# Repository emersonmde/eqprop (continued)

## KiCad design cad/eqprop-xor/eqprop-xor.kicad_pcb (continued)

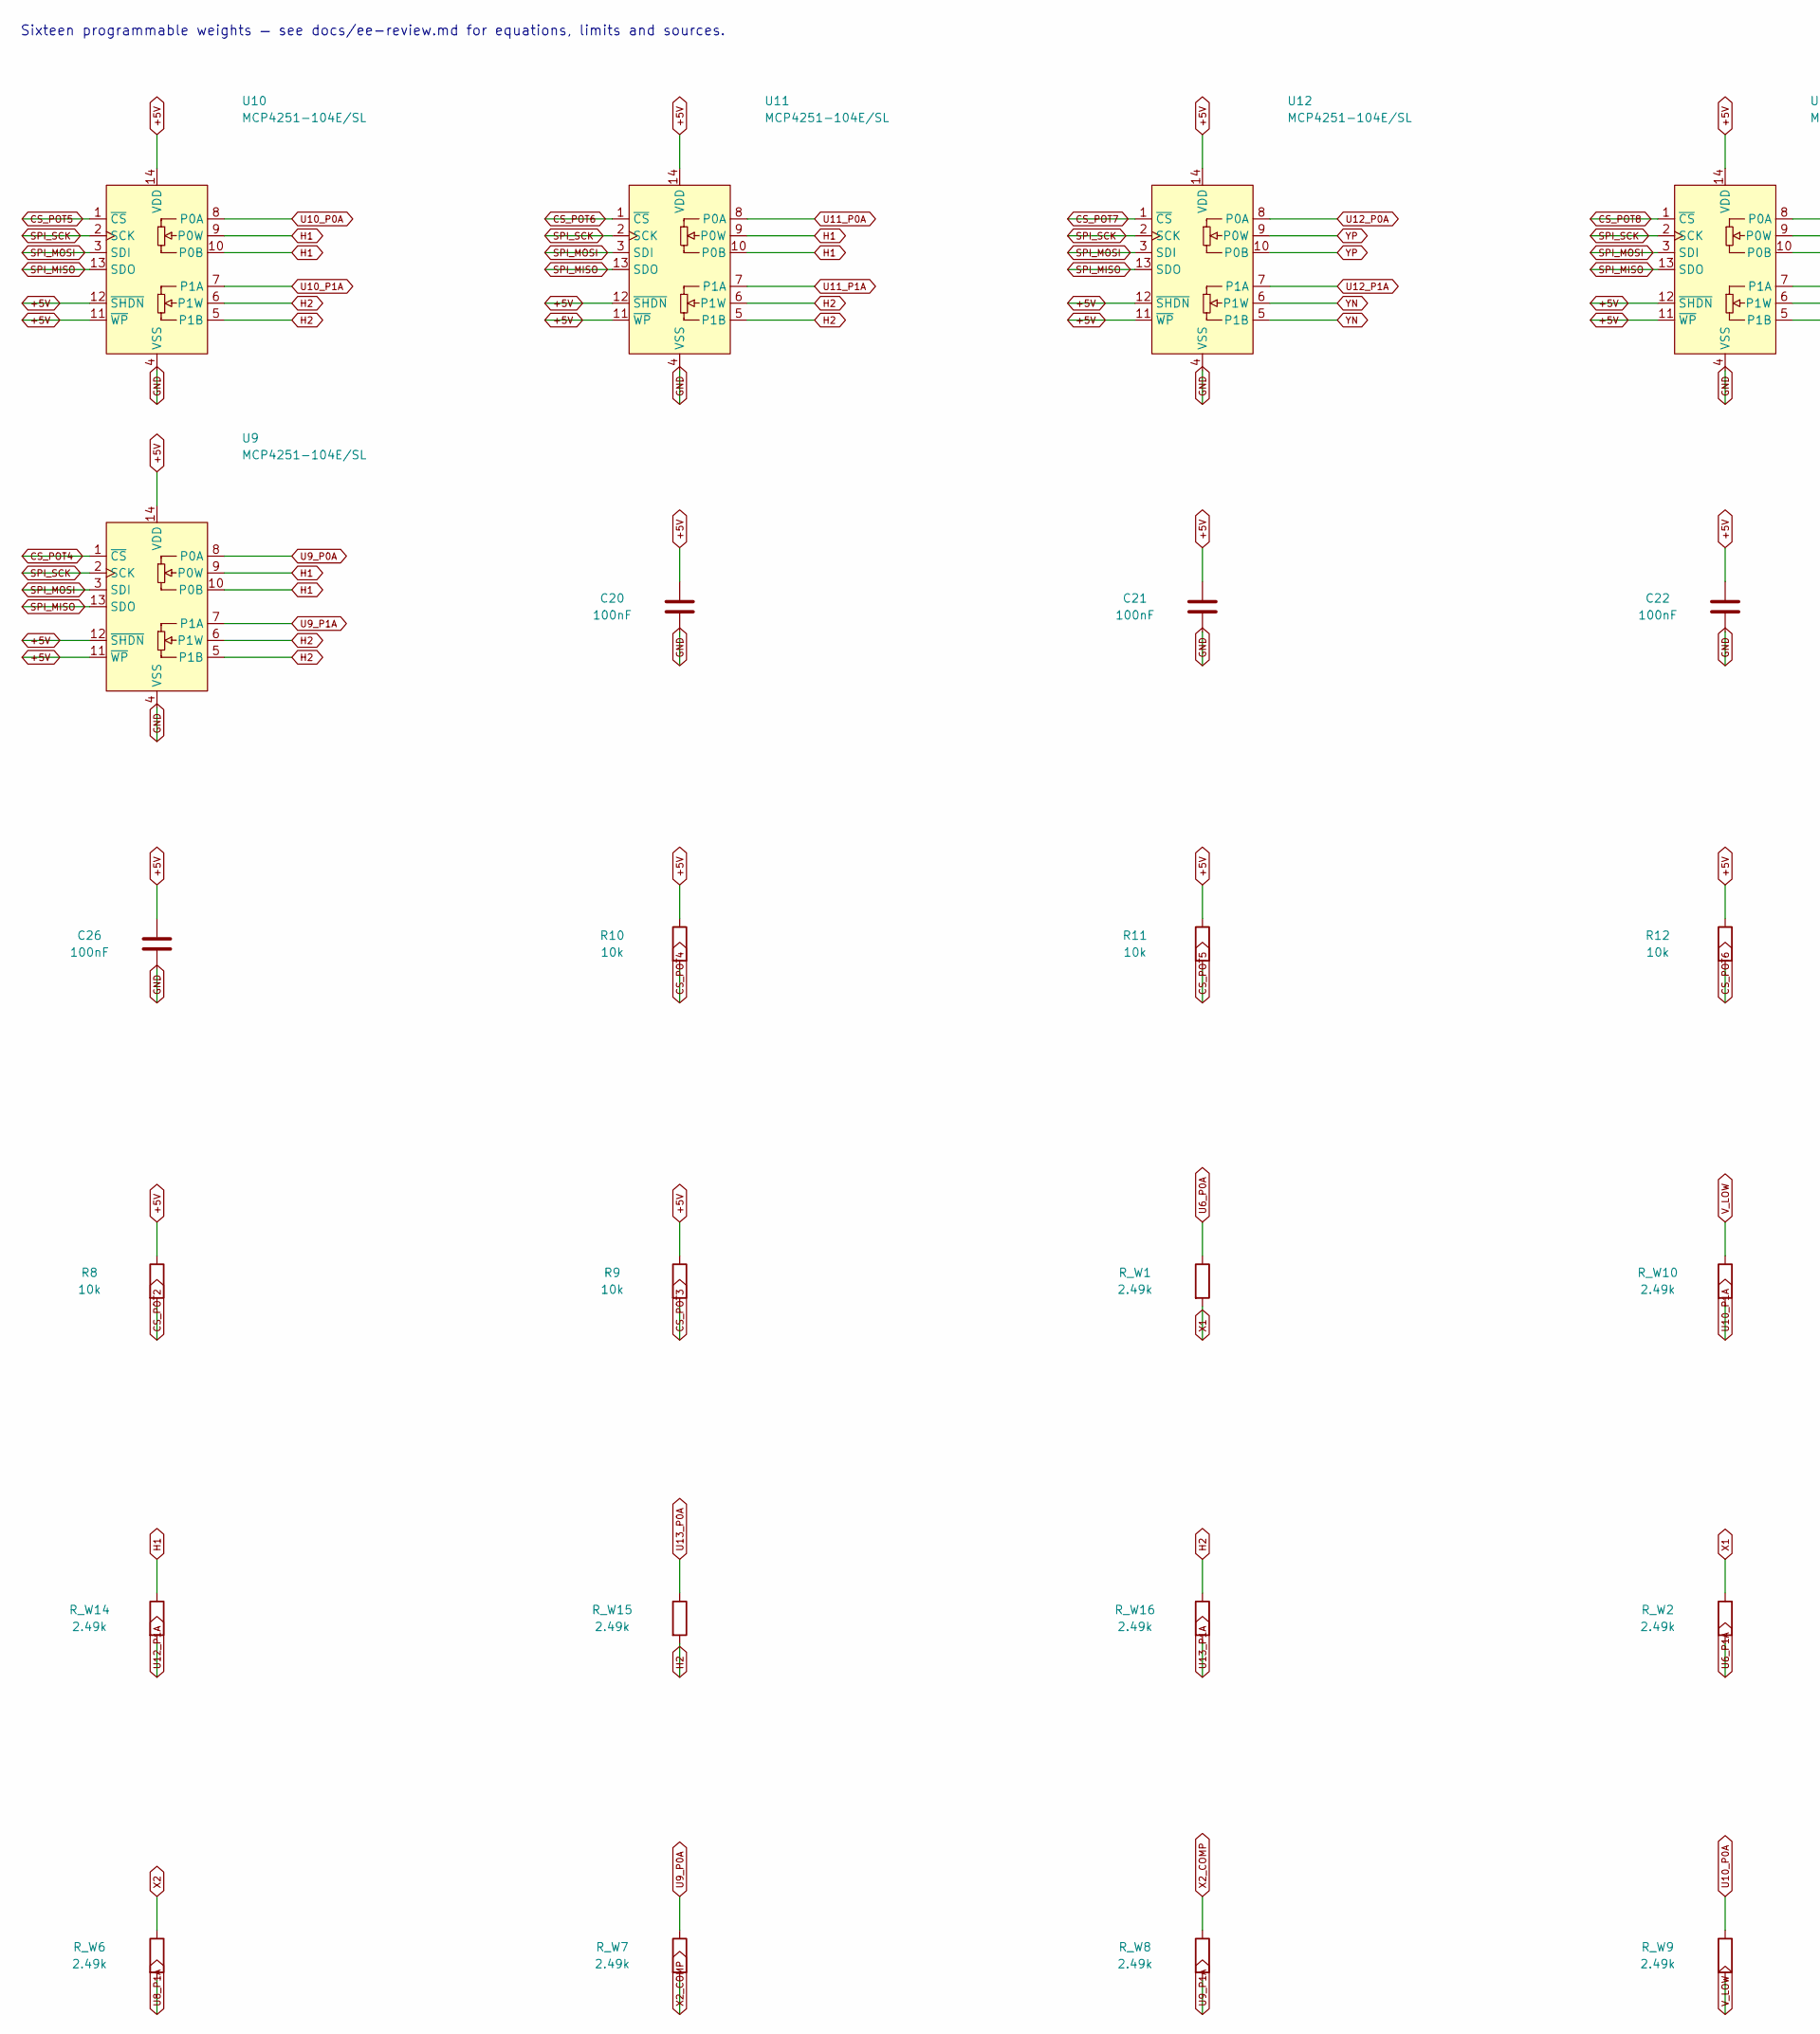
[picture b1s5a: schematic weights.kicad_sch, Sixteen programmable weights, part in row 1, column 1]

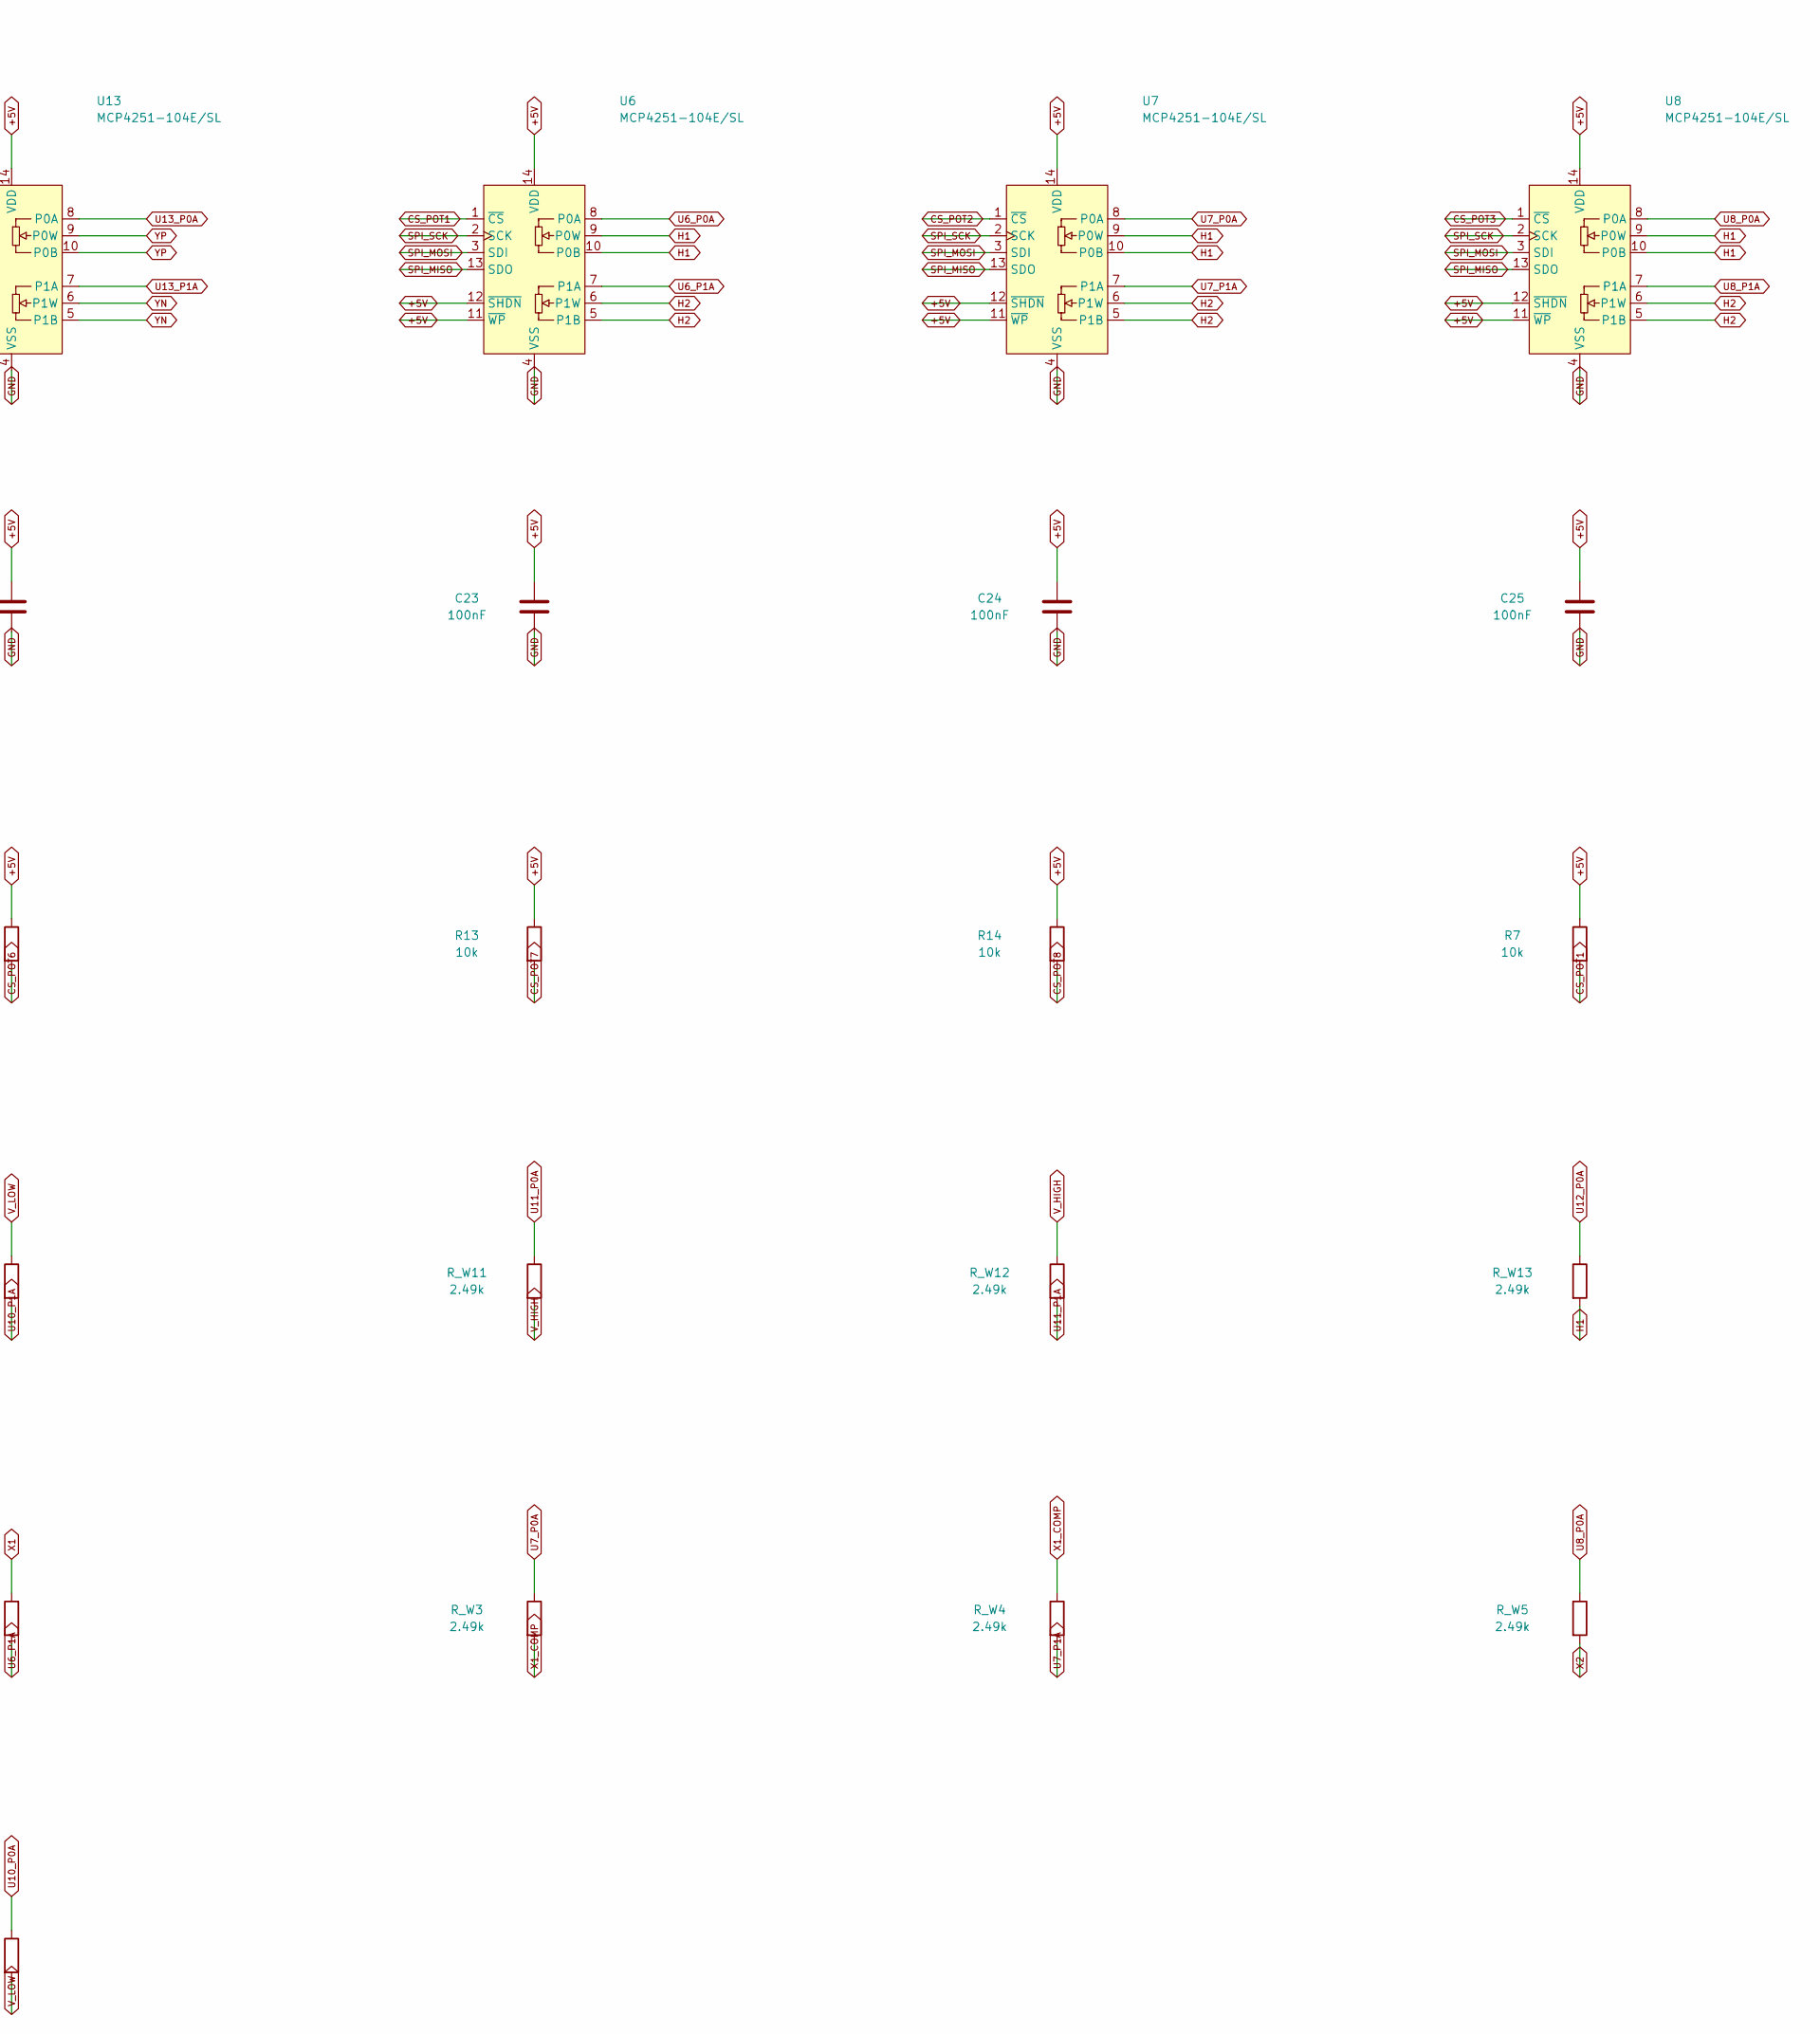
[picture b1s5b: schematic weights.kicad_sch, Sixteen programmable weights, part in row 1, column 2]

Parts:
C20, C21, C22, C23, C24, C25, C26: 100nF; C_0805_2012Metric; MPN C0805C104K5RACTU
R7, R8, R9, R10, R11, R12, R13, R14: 10k; R_0805_2012Metric; Tolerance 1%; MPN CRCW080510K0FKEA
R_W1, R_W2, R_W3, R_W4, R_W5, R_W6, R_W7, R_W8, R_W9, R_W10, R_W11, R_W12, R_W13, R_W14, R_W15, R_W16: 2.49k; R_0805_2012Metric; Tolerance 1%; MPN CRCW08052K49FKEA
U6, U7, U8, U9, U10, U11, U12, U13: MCP4251-104E/SL; SOIC-14_3.9x8.7mm_P1.27mm; MPN MCP4251-104E/SL

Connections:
+5V: C20.1, C21.1, C22.1, C23.1, C24.1, C25.1, C26.1, R7.1, R8.1, R9.1, R10.1, R11.1, R12.1, R13.1, R14.1, U6.11 (~WP), U6.12 (~SHDN), U6.14 (VDD), U7.11 (~WP), U7.12 (~SHDN), U7.14 (VDD), U8.11 (~WP), U8.12 (~SHDN), U8.14 (VDD), U9.11 (~WP), U9.12 (~SHDN), U9.14 (VDD), U10.11 (~WP), U10.12 (~SHDN), U10.14 (VDD), U11.11 (~WP), U11.12 (~SHDN), U11.14 (VDD), U12.11 (~WP), U12.12 (~SHDN), U12.14 (VDD), U13.11 (~WP), U13.12 (~SHDN), U13.14 (VDD); also elsewhere on the board
CS_POT1: R7.2, U6.1 (~CS); also elsewhere on the board
CS_POT2: R8.2, U7.1 (~CS); also elsewhere on the board
CS_POT3: R9.2, U8.1 (~CS); also elsewhere on the board
CS_POT4: R10.2, U9.1 (~CS); also elsewhere on the board
CS_POT5: R11.2, U10.1 (~CS); also elsewhere on the board
CS_POT6: R12.2, U11.1 (~CS); also elsewhere on the board
CS_POT7: R13.2, U12.1 (~CS); also elsewhere on the board
CS_POT8: R14.2, U13.1 (~CS); also elsewhere on the board
GND: C20.2, C21.2, C22.2, C23.2, C24.2, C25.2, C26.2, U6.4 (VSS), U7.4 (VSS), U8.4 (VSS), U9.4 (VSS), U10.4 (VSS), U11.4 (VSS), U12.4 (VSS), U13.4 (VSS); also elsewhere on the board
H1: R_W13.2, R_W14.1, U6.9 (P0W), U6.10 (P0B), U7.9 (P0W), U7.10 (P0B), U8.9 (P0W), U8.10 (P0B), U9.9 (P0W), U9.10 (P0B), U10.9 (P0W), U10.10 (P0B), U11.9 (P0W), U11.10 (P0B); also elsewhere on the board
H2: R_W15.2, R_W16.1, U6.5 (P1B), U6.6 (P1W), U7.5 (P1B), U7.6 (P1W), U8.5 (P1B), U8.6 (P1W), U9.5 (P1B), U9.6 (P1W), U10.5 (P1B), U10.6 (P1W), U11.5 (P1B), U11.6 (P1W); also elsewhere on the board
SPI_MISO: U6.13 (SDO), U7.13 (SDO), U8.13 (SDO), U9.13 (SDO), U10.13 (SDO), U11.13 (SDO), U12.13 (SDO), U13.13 (SDO); also elsewhere on the board
SPI_MOSI: U6.3 (SDI), U7.3 (SDI), U8.3 (SDI), U9.3 (SDI), U10.3 (SDI), U11.3 (SDI), U12.3 (SDI), U13.3 (SDI); also elsewhere on the board
SPI_SCK: U6.2 (SCK), U7.2 (SCK), U8.2 (SCK), U9.2 (SCK), U10.2 (SCK), U11.2 (SCK), U12.2 (SCK), U13.2 (SCK); also elsewhere on the board
U6_P0A: R_W1.1, U6.8 (P0A)
U6_P1A: R_W2.2, U6.7 (P1A)
U7_P0A: R_W3.1, U7.8 (P0A)
U7_P1A: R_W4.2, U7.7 (P1A)
U8_P0A: R_W5.1, U8.8 (P0A)
U8_P1A: R_W6.2, U8.7 (P1A)
U9_P0A: R_W7.1, U9.8 (P0A)
U9_P1A: R_W8.2, U9.7 (P1A)
U10_P0A: R_W9.1, U10.8 (P0A)
U10_P1A: R_W10.2, U10.7 (P1A)
U11_P0A: R_W11.1, U11.8 (P0A)
U11_P1A: R_W12.2, U11.7 (P1A)
U12_P0A: R_W13.1, U12.8 (P0A)
U12_P1A: R_W14.2, U12.7 (P1A)
U13_P0A: R_W15.1, U13.8 (P0A)
U13_P1A: R_W16.2, U13.7 (P1A)
V_HIGH: R_W11.2, R_W12.1; also elsewhere on the board
V_LOW: R_W9.2, R_W10.1; also elsewhere on the board
X1: R_W1.2, R_W2.1; also elsewhere on the board
X1_COMP: R_W3.2, R_W4.1; also elsewhere on the board
X2: R_W5.2, R_W6.1; also elsewhere on the board
X2_COMP: R_W7.2, R_W8.1; also elsewhere on the board
YN: U12.5 (P1B), U12.6 (P1W), U13.5 (P1B), U13.6 (P1W); also elsewhere on the board
YP: U12.9 (P0W), U12.10 (P0B), U13.9 (P0W), U13.10 (P0B); also elsewhere on the board

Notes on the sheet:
Sixteen programmable weights — see docs/ee-review.md for equations, limits and sources.

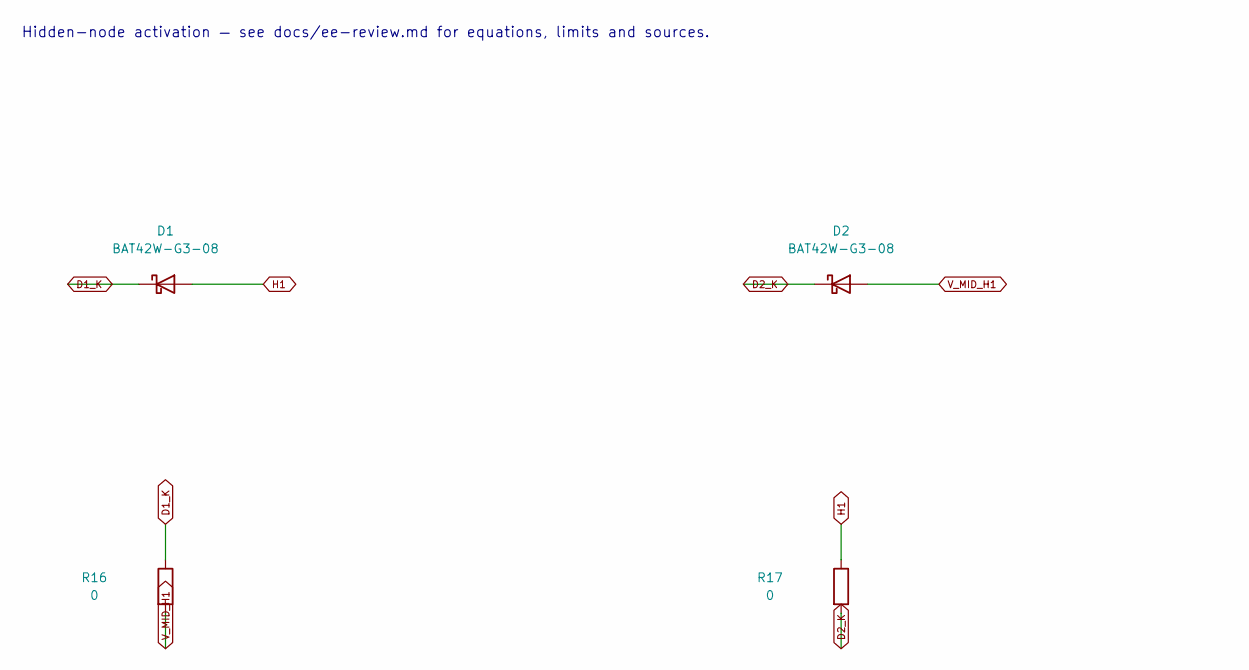
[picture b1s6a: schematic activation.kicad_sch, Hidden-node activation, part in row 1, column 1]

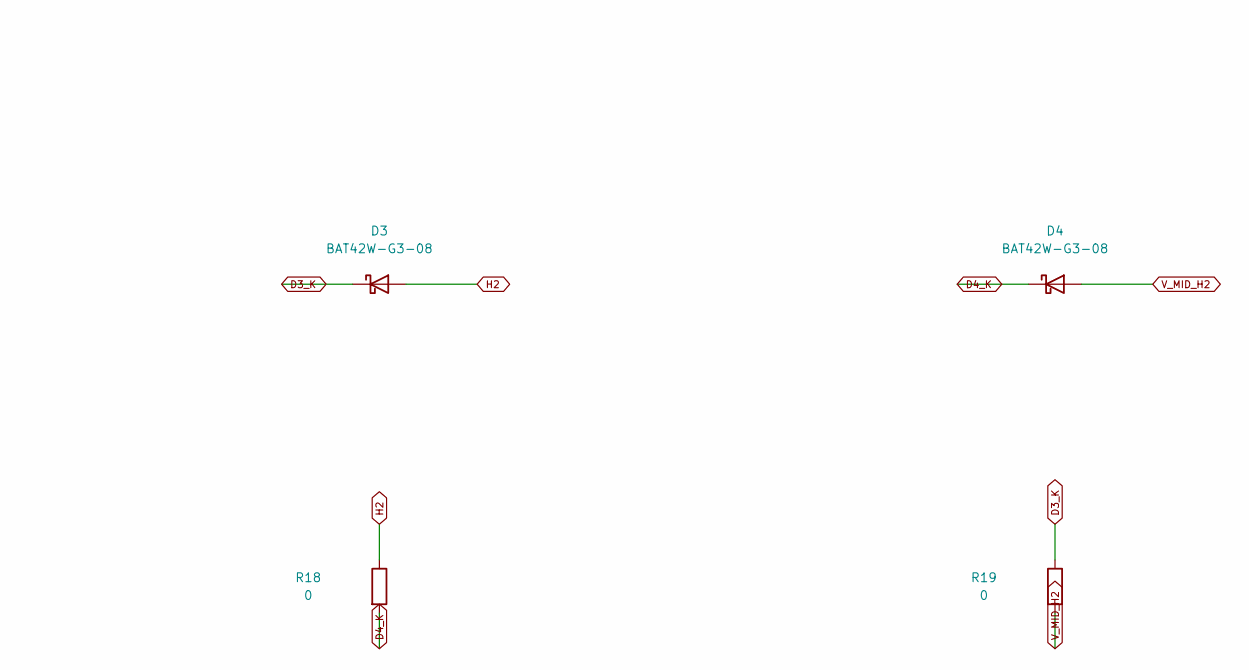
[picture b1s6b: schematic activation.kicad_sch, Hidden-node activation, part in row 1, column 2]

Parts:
D1, D2, D3, D4: BAT42W-G3-08; D_SOD-123; MPN BAT42W-G3-08
R16, R17, R18, R19: 0; R_0805_2012Metric; Tolerance Jumper; MPN CRCW08050000Z0EA

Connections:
D1_K: D1.1 (K), R16.1
D2_K: D2.1 (K), R17.2
D3_K: D3.1 (K), R19.1
D4_K: D4.1 (K), R18.2
H1: D1.2 (A), R17.1; also elsewhere on the board
H2: D3.2 (A), R18.1; also elsewhere on the board
V_MID_H1: D2.2 (A), R16.2; also elsewhere on the board
V_MID_H2: D4.2 (A), R19.2; also elsewhere on the board

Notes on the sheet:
Hidden-node activation — see docs/ee-review.md for equations, limits and sources.

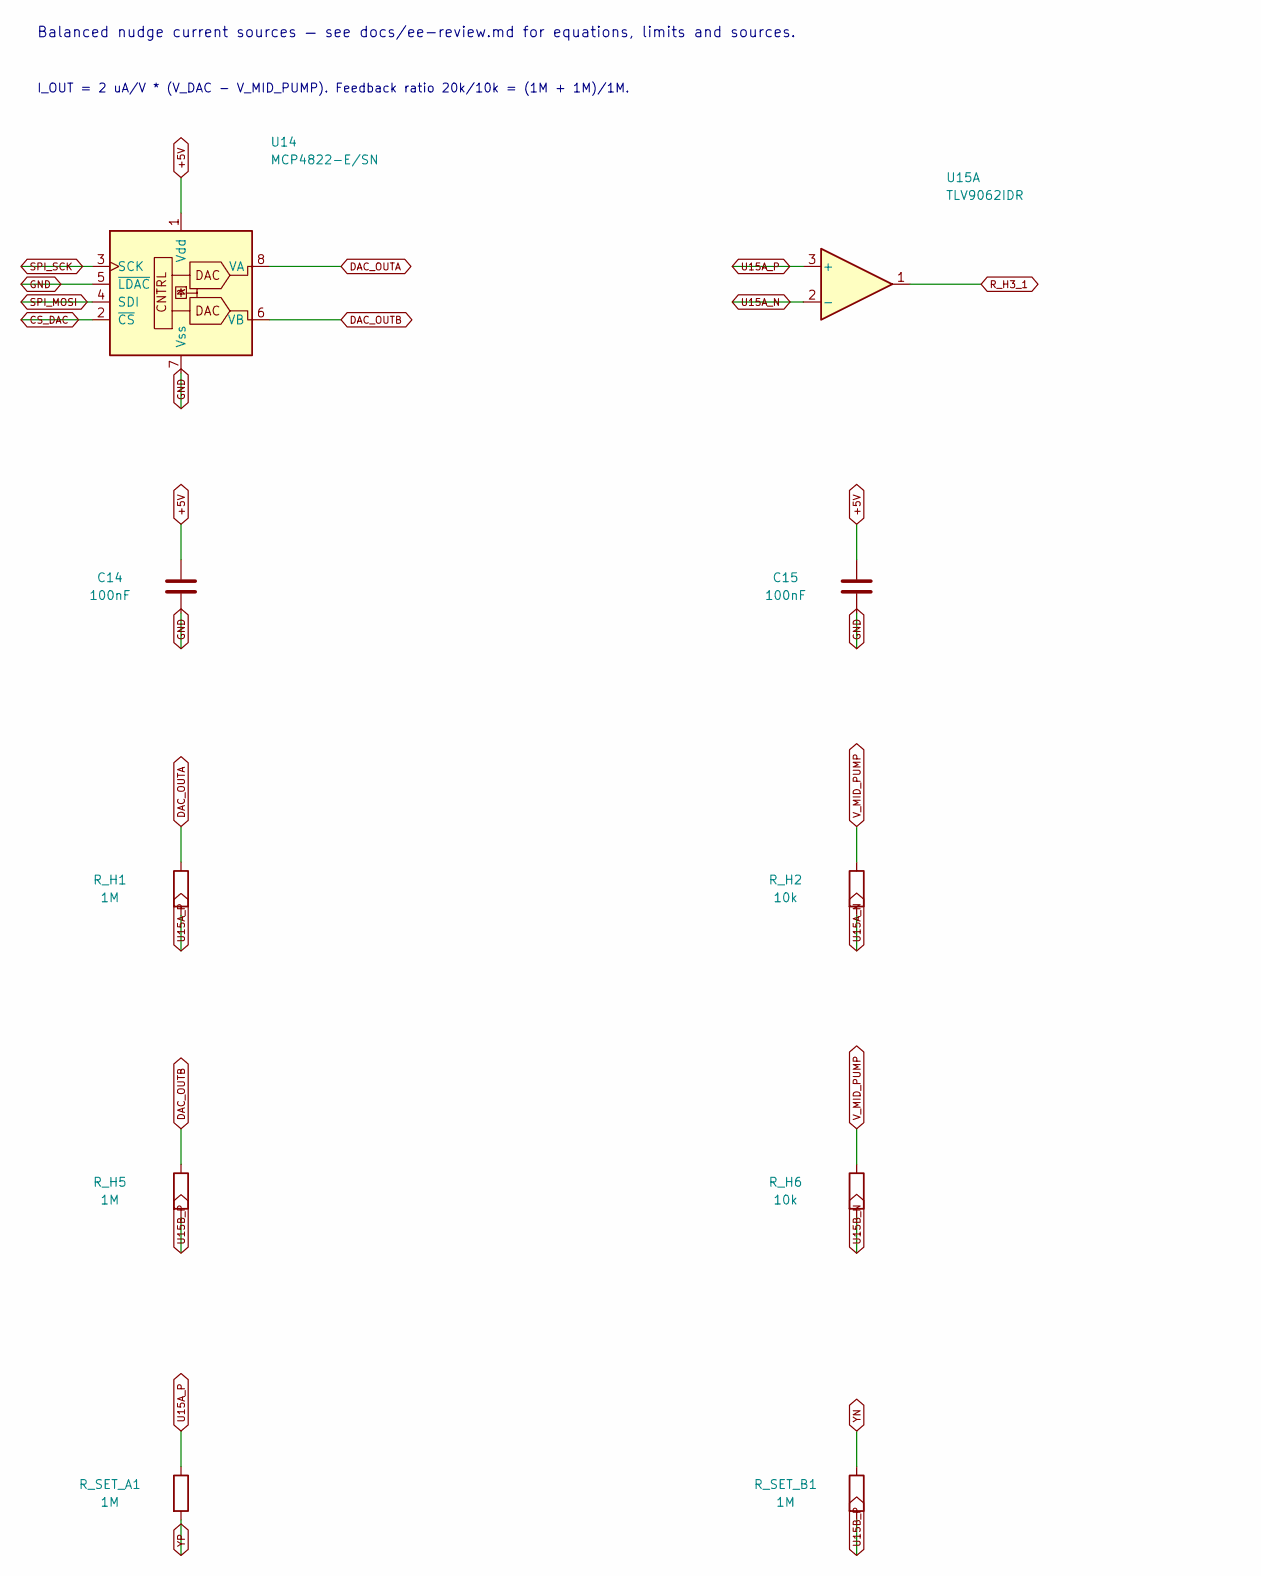
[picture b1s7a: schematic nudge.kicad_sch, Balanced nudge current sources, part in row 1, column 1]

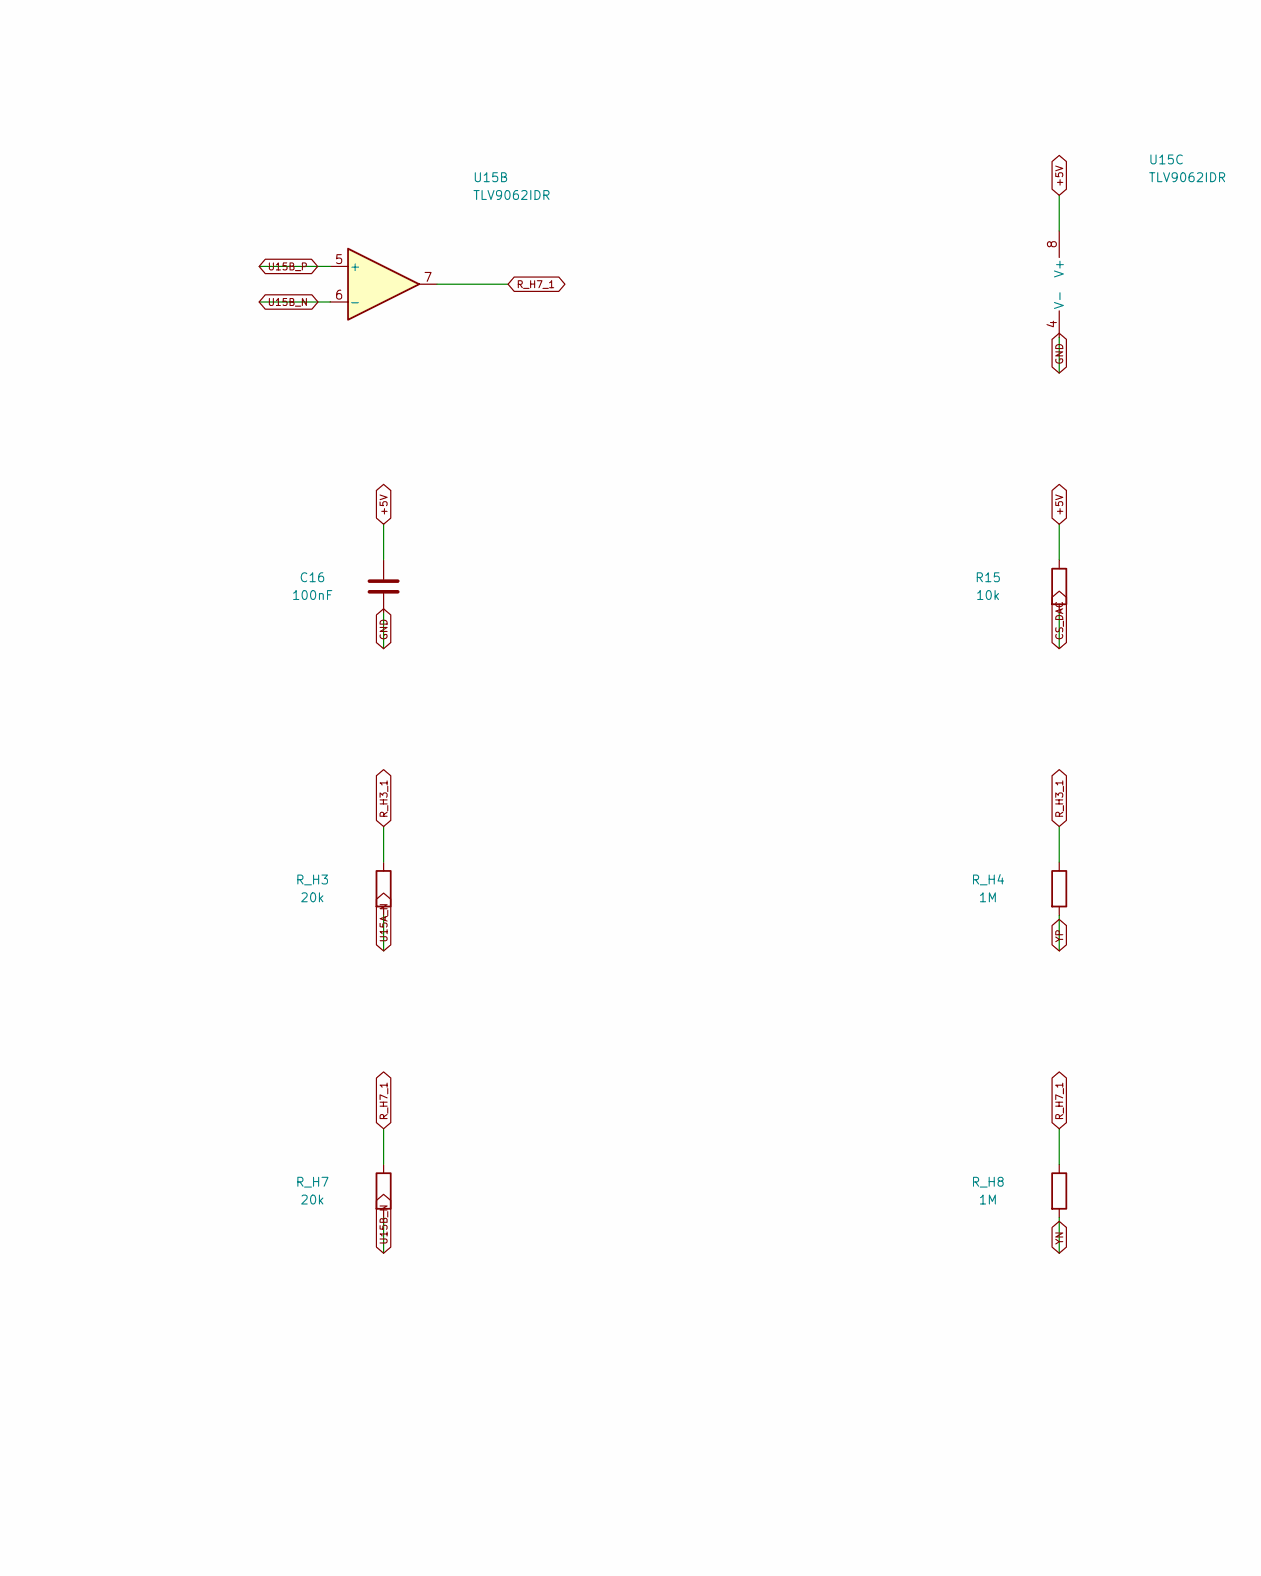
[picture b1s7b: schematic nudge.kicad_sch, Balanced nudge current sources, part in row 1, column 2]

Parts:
C14, C15, C16: 100nF; C_0805_2012Metric; MPN C0805C104K5RACTU
R15: 10k; R_0805_2012Metric; Tolerance 1%; MPN CRCW080510K0FKEA
R_H1, R_H4, R_H5, R_H8: 1M; R_0805_2012Metric; Tolerance 0.1%; MPN TNPW08051M00BEEA
R_H2, R_H6: 10k; R_0805_2012Metric; Tolerance 0.1%; MPN TNPW080510K0BEEA
R_H3, R_H7: 20k; R_0805_2012Metric; Tolerance 0.1%; MPN TNPW080520K0BEEA
R_SET_A1: 1M; R_0805_2012Metric; Tolerance 0.1%; MPN TNPW08051M00BEEA
R_SET_B1: 1M; R_0805_2012Metric; Tolerance 0.1%; MPN TNPW08051M00BEEA
U14: MCP4822-E/SN; SOIC-8_3.9x4.9mm_P1.27mm; MPN MCP4822-E/SN
U15: TLV9062IDR; SOIC-8_3.9x4.9mm_P1.27mm; MPN TLV9062IDR

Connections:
+5V: C14.1, C15.1, C16.1, R15.1, U14.1 (Vdd), U15.8 (V+); also elsewhere on the board
CS_DAC: R15.2, U14.2 (~CS); also elsewhere on the board
DAC_OUTA: R_H1.1, U14.8 (VA); also elsewhere on the board
DAC_OUTB: R_H5.1, U14.6 (VB); also elsewhere on the board
GND: C14.2, C15.2, C16.2, U14.5 (~LDAC), U14.7 (Vss), U15.4 (V-); also elsewhere on the board
R_H3_1: R_H3.1, R_H4.1, U15.1
R_H7_1: R_H7.1, R_H8.1, U15.7
SPI_MOSI: U14.4 (SDI); also elsewhere on the board
SPI_SCK: U14.3 (SCK); also elsewhere on the board
U15A_N: R_H2.2, R_H3.2, U15.2 (-)
U15A_P: R_H1.2, R_SET_A1.1, U15.3 (+)
U15B_N: R_H6.2, R_H7.2, U15.6 (-)
U15B_P: R_H5.2, R_SET_B1.2, U15.5 (+)
V_MID_PUMP: R_H2.1, R_H6.1; also elsewhere on the board
YN: R_H8.2, R_SET_B1.1; also elsewhere on the board
YP: R_H4.2, R_SET_A1.2; also elsewhere on the board

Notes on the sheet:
Balanced nudge current sources — see docs/ee-review.md for equations, limits and sources.
I_OUT = 2 uA/V * (V_DAC - V_MID_PUMP). Feedback ratio 20k/10k = (1M + 1M)/1M.
